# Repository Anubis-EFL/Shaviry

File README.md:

# Shaviry
Adaptador todo en uno del puerto de vídeo de Amiga a VGA con switch de monitores automático y amplificador RGB para minimizar las barras verticales (jail bars) típicas en LCD.

****Advertencia: Esto no es un Scandoubler, tu monitor debe soportar 15khz.****

Sobre el nombre: Shaviry es nuestro agapornis que lleva con nosotros 15 años así que decidí ponerle su nombre para hacerle un homenaje y buscarle un acrónimo, algo forzado pero que mas o menos encaja.
En principio hay dos opciones:

  1) ****SH****arp ****A****miga ****V****ideo ****I****nput switche****R**** s****Y****stem.
  2) ****SH****ort for ****A****miga ****V****ideo ****I****nput switche****R**** s****Y****stem.

Las pruebas han sido en un monitor DELL SE2722HX con una máquina AGA y los amplificadores THS7374 y THS7376.

Con el THS7374 y el filtro activo las barras todavía se perciben un poco y la imagen es un poco borrosa debido a que el ancho de banda del filtro es de solo 9,5mhz.

Con el THS7376 son casi imperceptibles aunque, en ocasiones, las sigo notando si las busco activamente. En uso normal (juegos, demos... etc) la mayoría del tiempo ni las percibo.

No se aprecian en una foto de la pantalla (o casi), por lo que no se si es ya obsesión mía. Por tanto, hasta que pueda hacer mas pruebas, me quedaría con la segunda opción.

De todas formas ahí va la típica foto. Con THS7376 y el filtro activo.

El adaptador tiene unos jumpers para configurar su funcionamiento de dos formas:

 1) Como solo adaptador a VGA por si no dispones de tarjeta gráfica o pistorm (con adaptador de HDMI a VGA)
 2)  Como switch automático de entradas controlado por una señal de 5v.
 
   Esta señal puede ser la que envía switchcontrol por la CIA o el puerto paralelo. En el caso de pistorm puedes sustituir switchcontrol por la opción del driver P96.
  
   Si no quieres usar esas opciónes siempre puedes accionar la conmutación insertando una señal de 5v controlandola con un interruptor, arduino o lo que se te ocurra.

La señal de 5v de conmutación está aislada con un optoacoplador para evitar sustos.

Tambien hay un jumper soldable donde elegir activar o desactivar el filtro del amplificador, hay que elegir una u otra opción, no se debe dejar flotante. Con el THS7376 es recomendable dejarlo activo.

El cambio en un monitor CRT es instantaneo, aunque en un LCD se demora un poco mas.

****Lista de componentes:****
 | Componente | Valor | Tamaño | Cantidad |
 | --- | --- | --- | --- |
 | R1, R2, R3, R4, R5, R6 | 75r | 0603 | 6 |
 | R7 | 1k | 0603 | 1 |
 | R8 | 10k | 0603 | 1 |
 | C1 | 10nf | 0603 | 1 |
 | C2, C3, C4 | 100nf | 0603 | 3 |
 | FB1, FB2, FB3, FB4, FB5 | Ferrita | 0603 | 5 |
 | U1 | 74HCT14 | SO-14 | 1 |
 | U2 | SGM4717 | MSOP-10 | 1 |
 | U3 | THS7373/THS7374/THS7376 | TSSOP-14 | 1 |
 | U4 | SGM330A | SSOP-16 | 1 |
 | U5 | PC817/EL817 | DIP-4 SMD | 1 |
 | J1 | DB23 Hembra | Para cable | 1 |
 | J2, J3 | DB15HD Hembra | Para PCB 3,08mm | 2 |
 | J4 | Tira de 3x2 pines | 2,54mm | 1 |
 | Otros | Jumpers | | 2 |

Ante todo señalar que soy simplemente un aficionado a la electrónica y es mi primer proyecto en KiCad, así que puede haber cosas mejor hechas.

Mis agradecimientos a Alberto Benitez (Lince / EA4GGE) por sus consejos, sin los cuales probablemente todavía me estaría comiendo la cabeza sobre como enrutar la pcb.
  
## Revisiones:

Las revisiones se nombran como REV seguido de la fecha en formato dd/mm/aaaa

  ****REV19122023****

Revisión inicial. (Publicada el 31/12/2023)

 ****REV02012024****

Cambiadas las entradas y salidas del amplificador para que sea totalmente compatible con los THS7373, 7HS7374 Y THS7376.

 ****REV21012024****
 
Cambiado el punto de conexión de la pista de la entrada G del RGB del Amiga al amplificador. No hay cambios en funcionalidad ya que va al mismo sítio pero por otro lado.

 ****REV23012024****

 Eliminadas todas las islas de masa sin conectar.

## Agunas imágenes.

Shaviry Con Shaviry

Shaviry diciendole a Shaviry quien manda.

Algunas Vistas:

Junto al adaptador de Commodore. Si, está muy guarro, pero lleva mas de 25 años enchufado a mi Amiga 4000 y ni le he echado cuenta.

## Videos

En un monitor LCD (DELL SE2722HX)

https://github.com/Anubis-EFL/Shaviry/assets/154557850/1416b5dd-fce8-4823-900b-c1d1edef9626

En un monitor CRT (Microvitec 1438) El RTG sale desplazado por no tener totalmente ajustado el modo hdmi de la pistorm32.

https://github.com/Anubis-EFL/Shaviry/assets/154557850/919e8689-20b6-4c1b-af77-966b4a6acc1a

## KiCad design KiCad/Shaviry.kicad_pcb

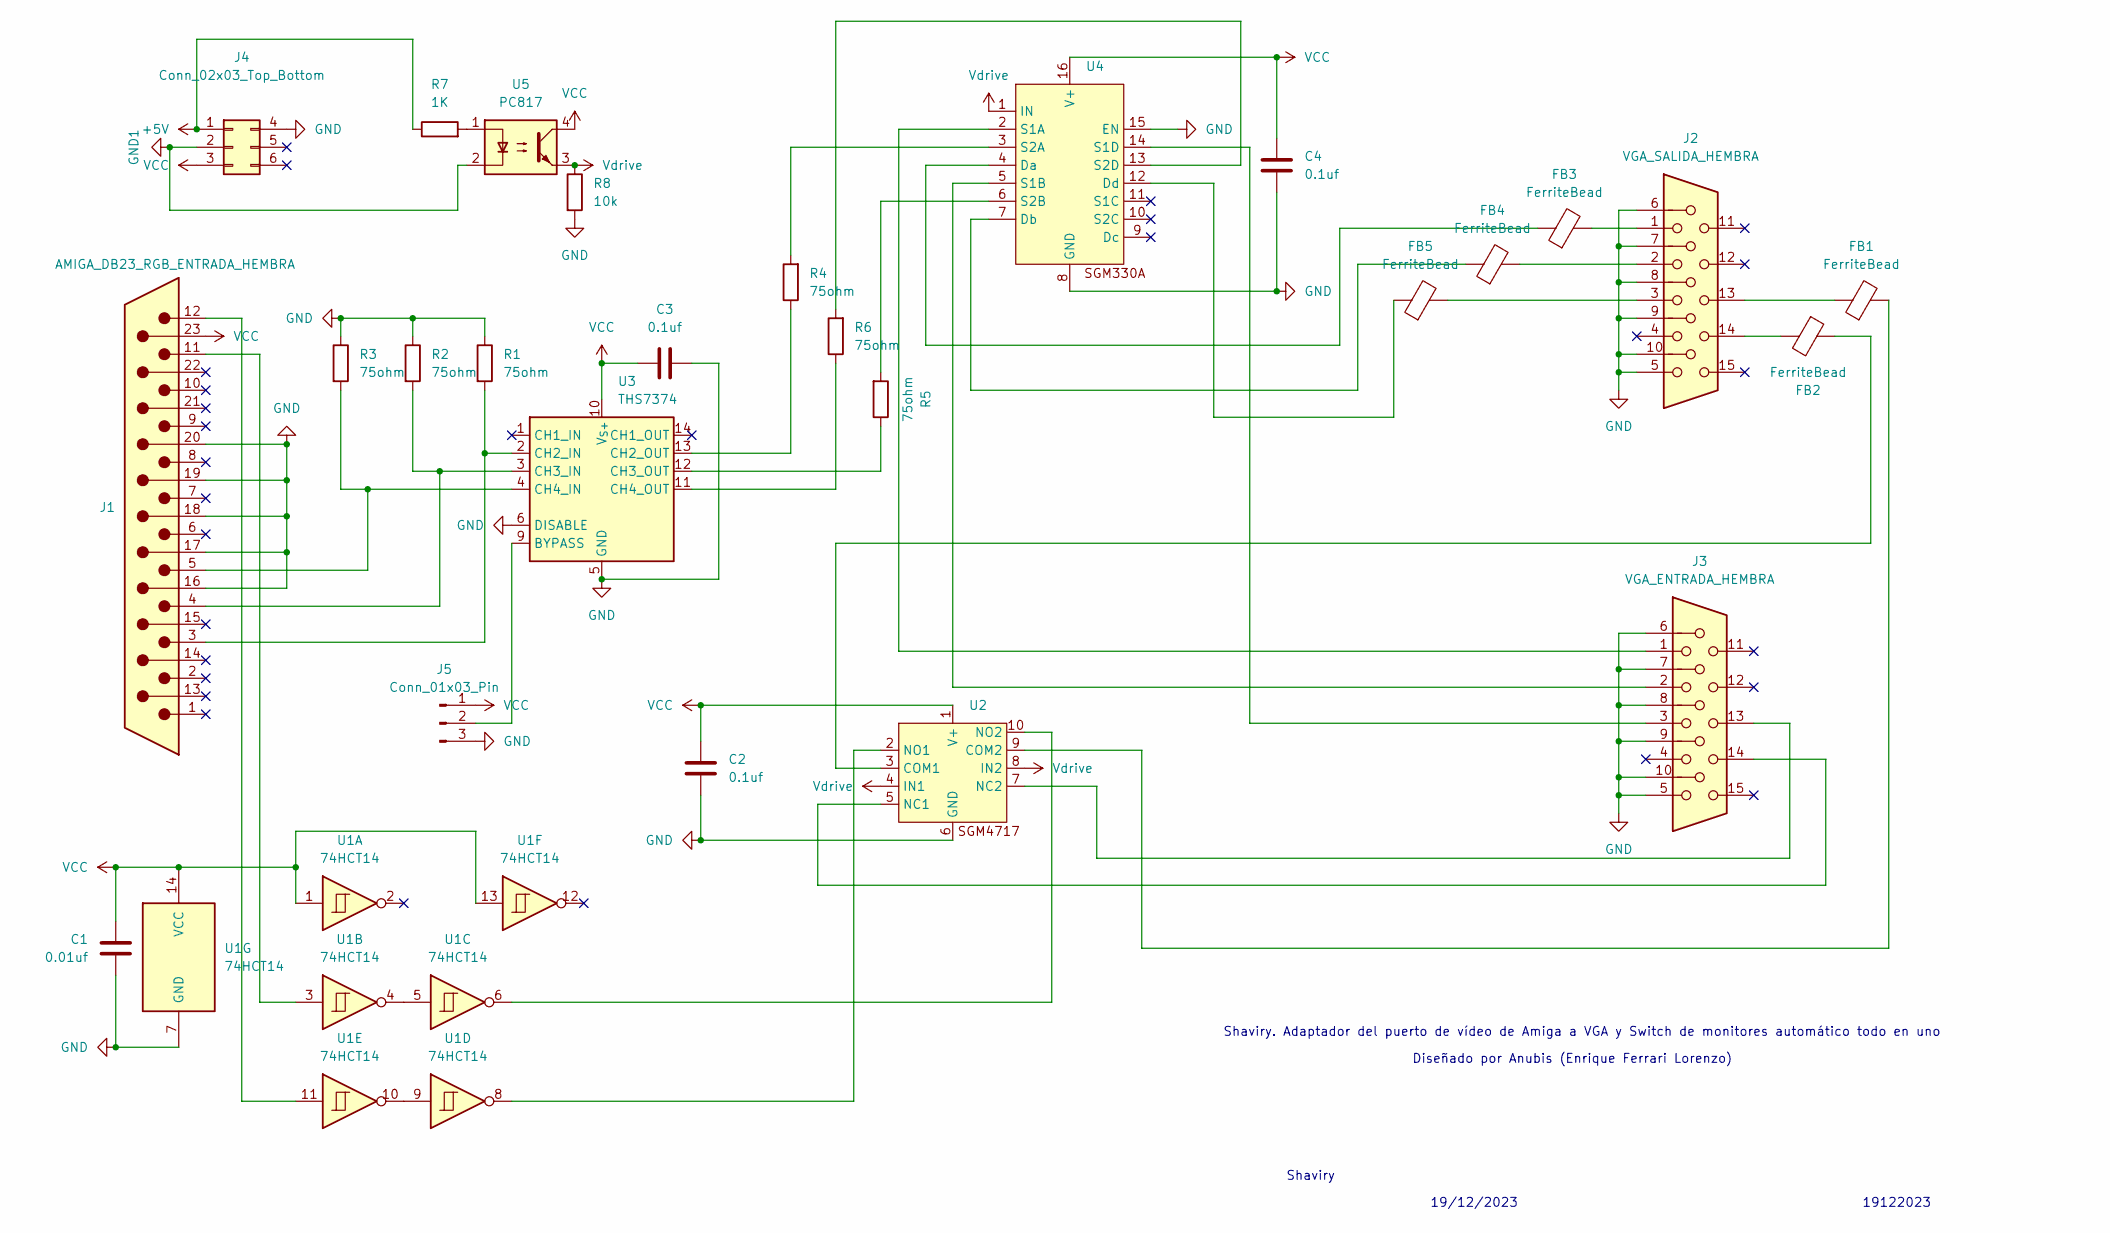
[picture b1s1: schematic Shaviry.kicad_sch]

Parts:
C1: 0.01uf; C_0603_1608Metric
C2, C3, C4: 0.1uf; C_0603_1608Metric
FB1, FB2, FB3, FB4, FB5: FerriteBead; R_0603_1608Metric_Pad0.98x0.95mm_HandSolder
J1: AMIGA_DB23_RGB_ENTRADA_HEMBRA; DB_23_RGB_Female_EdgeMount_P2.77mm
J2: VGA_SALIDA_HEMBRA; DSUB-15-HD_Female_Horizontal_P2.29x1.98mm_EdgePinOffset3.03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
J3: VGA_ENTRADA_HEMBRA; DSUB-15-HD_Female_Horizontal_P2.29x1.98mm_EdgePinOffset3.03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
J4: Conn_02x03_Top_Bottom; PinHeader_2x03_P2.54mm_Vertical
J5: Conn_01x03_Pin; SolderJumper-3_P1.3mm_Open_Pad1.0x1.5mm
R1, R2, R3, R4, R5, R6: 75ohm; R_0603_1608Metric_Pad0.98x0.95mm_HandSolder
R7: 1K; R_0603_1608Metric_Pad0.98x0.95mm_HandSolder
R8: 10k; R_0603_1608Metric_Pad0.98x0.95mm_HandSolder
U1: 74HCT14; SO-14_3.9x8.65mm_P1.27mm
U2: MSOP-10_3x3mm_P0.5mm
U3: THS7374; TSSOP-14_4.4x5mm_P0.65mm
U4: SSOP-16_4.4x5.2mm_P0.65mm
U5: PC817; DIP-4_W8.89mm_SMDSocket_LongPads

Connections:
+5V: J4.1, R7.1
GND: C1.2, C2.2, C3.2, C4.2, J1.16 (REDGND), J1.17 (GREENGND), J1.18 (BLUEGND), J1.19 (CHVSYNCGND), J1.20 (GND), J2.0, J2.5, J2.6, J2.7, J2.8, J2.9, J2.10, J3.0, J3.5, J3.6, J3.7, J3.8, J3.9, J3.10, J4.4, J5.3, R1.1, R2.1, R3.1, R8.2, U1.7 (GND), U2.6 (GND), U3.5 (GND), U3.6 (DISABLE), U4.8 (GND), U4.15 (EN)
GND1: J4.2, U5.2
unnamed: FB1.1, J2.13
unnamed: FB2.2, J2.14
unnamed: FB3.2, J2.1
unnamed: FB4.2, J2.2
unnamed: FB5.2, J2.3
unnamed: J1.5 (BLUE), R3.2, U3.4 (CH4_IN)
unnamed: J1.4 (GREEN), R2.2, U3.3 (CH3_IN)
unnamed: J1.3 (RED), R1.2, U3.2 (CH2_IN)
unnamed: J1.11 (/HSYNC), U1.3
unnamed: J1.12 (/VSYNC), U1.11
unnamed: J5.2, U3.9 (BYPASS)
unnamed: R7.2, U5.1
unnamed: U1.4, U1.5
unnamed: U1.9, U1.10
unnamed: FB2.1, U2.3 (COM1)
unnamed: FB1.2, U2.9 (COM2)
unnamed: J3.14, U2.5 (NC1)
unnamed: J3.13, U2.7 (NC2)
unnamed: U1.8, U2.2 (NO1)
unnamed: U1.6, U2.10 (NO2)
unnamed: R4.1, U3.13 (CH2_OUT)
unnamed: R5.1, U3.12 (CH3_OUT)
unnamed: R6.1, U3.11 (CH4_OUT)
unnamed: FB3.1, U4.4 (Da)
unnamed: FB4.1, U4.7 (Db)
unnamed: FB5.1, U4.12 (Dd)
unnamed: J3.1, U4.2 (S1A)
unnamed: J3.2, U4.5 (S1B)
unnamed: J3.3, U4.14 (S1D)
unnamed: R4.2, U4.3 (S2A)
unnamed: R5.2, U4.6 (S2B)
unnamed: R6.2, U4.13 (S2D)
VCC: C1.1, C2.1, C3.1, C4.1, J1.23 (+5v), J4.3, J5.1, U1.1, U1.13, U1.14 (VCC), U2.1 (V+), U3.10 (V_{S+}), U4.16 (V+), U5.4
Vdrive: R8.1, U2.4 (IN1), U2.8 (IN2), U4.1 (IN), U5.3

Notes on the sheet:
19/12/2023
Shaviry. Adaptador del puerto de vídeo de Amiga a VGA y Switch de monitores automático todo en uno
19122023
Diseñado por Anubis (Enrique Ferrari Lorenzo)
Shaviry

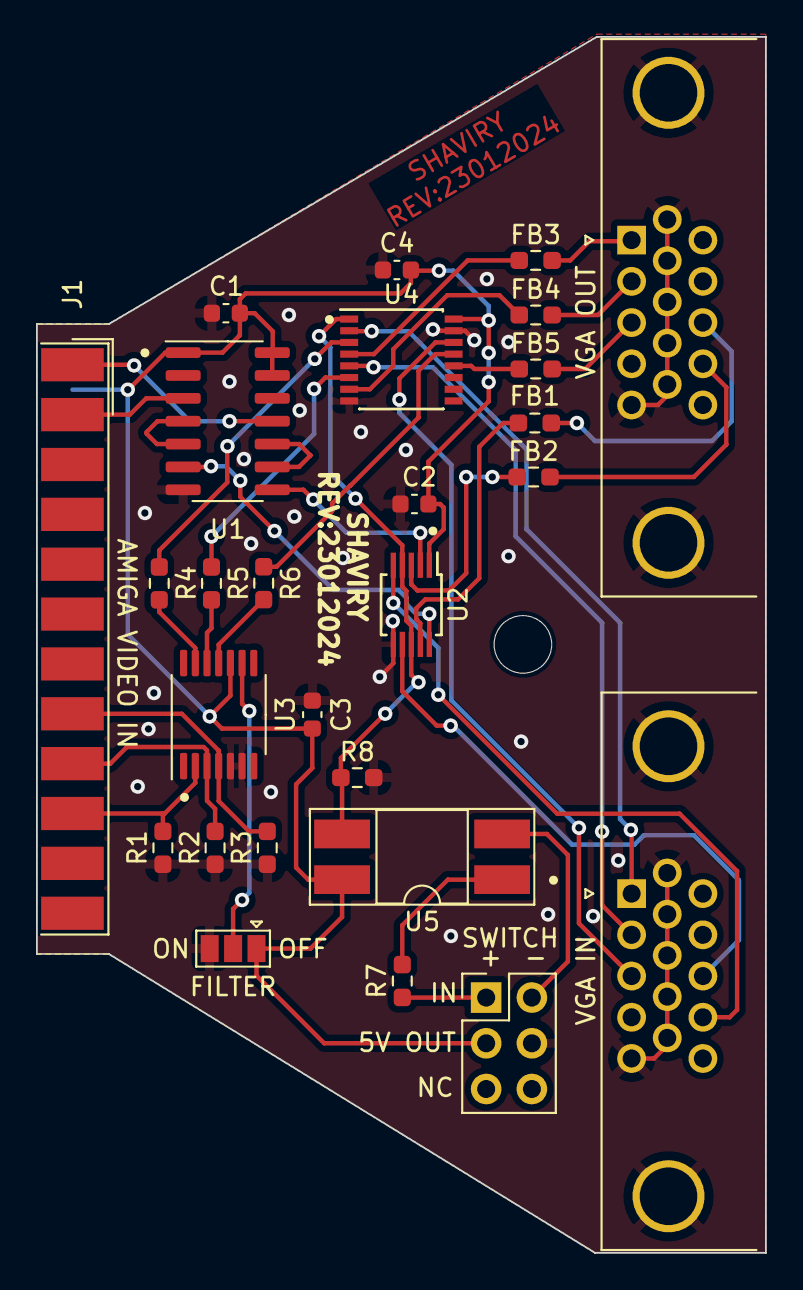
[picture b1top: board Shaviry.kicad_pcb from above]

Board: 2 copper layers, 40.5 x 67.6 mm, 27 parts (0 on the bottom side), 37 nets.

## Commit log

2023-12-31 Create LICENSE
2023-12-31 Update LICENSE
2024-01-02 Add files via upload
    Gerbers de la revisión 02012024.
    Cambiadas las entradas y salidas del amplificador para que sea totalmente compatible con los THS7373, THS7374 y THS7376
2024-01-02 Update README.md
    Añadida lista de componentes (por revisar)
2024-01-04 Add files via upload
    Cambiada la fecha en la serigrafía inferior
2024-01-04 Add files via upload
    Actualizado el gerber con la nueva fecha
2024-01-08 Update README.md
    Actualizado el vídeo del CRT, ya no produce epilepsia
2024-01-21 Update README.md
    Añadidas impresiones con el ths7376
2024-01-21 Add files via upload
    Cambiado el punto de conexión de la pista de la entrada G del RGB del Amiga al amplificador. No hay cambios en funcionalidad ya que va al mismo sítio pero por otro lado.
2024-01-23 Add files via upload
    Eliminadas todas las islas de masa sin conectar
2024-02-02 Add files via upload
    Añadida foto de la pantalla de arranque de un 1200 en un monitor LCD con Shaviry y THS7376 con el filtro activo
2024-02-03 Add files via upload
    La foto anterior estaba inclinada, cambiada por una que está nivelada
